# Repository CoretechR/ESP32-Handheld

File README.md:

# ESP32-Handheld

Tested with Arduino for ESP32 Core 1.0.4

The lastes firmware needs the modified Adafruit SharpMem library. This library includes a hugely faster screen clearing function and hardware SPI.

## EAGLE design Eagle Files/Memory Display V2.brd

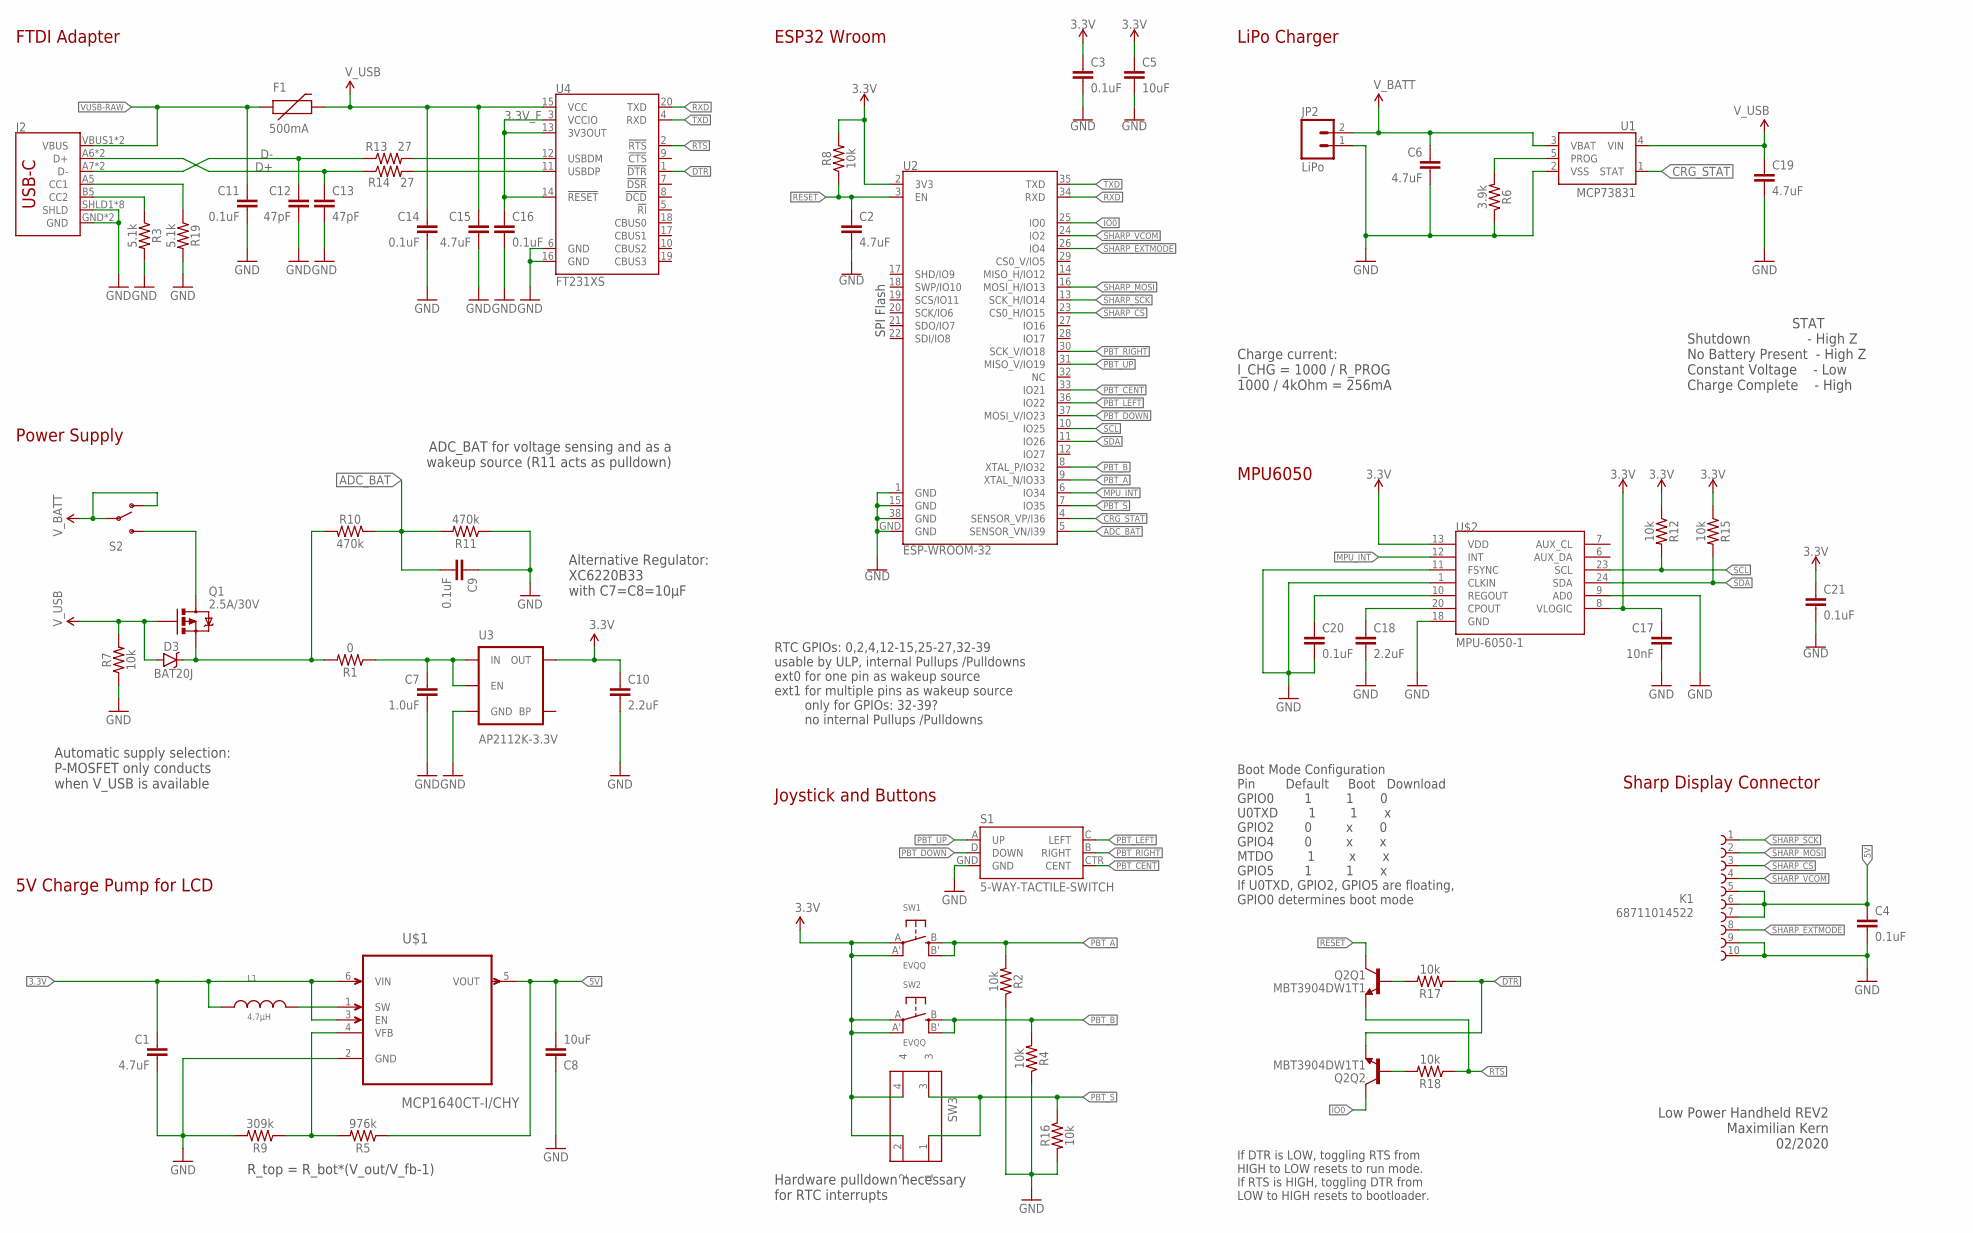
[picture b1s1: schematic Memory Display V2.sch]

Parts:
C1, C2, C6, C19: 4.7uF; 0603
C3, C4, C9, C11, C14, C16, C20, C21: 0.1uF; 0603
C5, C8: 10uF; 0603
C7: 1.0uF; 0805
C10, C18: 2.2uF; 0805
C12, C13: 47pF; 0603
C15: 4.7uF; 0603-CAP
C17: 10nF; 0603
D3: BAT20J; SOD-323
F1: 500mA; PTC-1206
J2: USB_C16PIN; USB-C-16P
JP2: LiPo; JST-2-PTH
K1: 68711014522
L1: 4.7µH; WE-TPC_2811/2813_OLD
Q1: 2.5A/30V; SOT23-3
Q2: MBT3904DW1T1; SC70-6
R1: 0; 0603
R2, R4, R7, R8, R12, R15, R16, R17, R18: 10k; 0603
R3, R19: 5.1k; 0603
R5: 976k; 0603
R6: 3.9k; 0603
R9: 309k; 0603
R10, R11: 470k; 0603
R13, R14: 27; 0603
S1: 5-WAY-TACTILE-SWITCH; JOYSTICK_MINI
S2: SWITCH-SPDT-SMD-A; SWITCH-SPST-SMD-A
SW1, SW2: EVQQ; EVQ-Q2_SMALLER
SW3: 434331045822
U1: MCP73831; SOT23-5
U2: ESP-WROOM-32
U3: AP2112K-3.3V; SOT23-5
U4: FT231XS; SSOP20_L
U$1: MCP1640CT-I/CHY; SOT95P270X145-6N
U$2: MPU-6050-1; QFN-24-4MM2

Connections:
3.3V: C1.1, C3.1, C5.1, C10.1, C17.1, C21.1, L1.1, R8.2, R12.1, R15.1, SW1.A, SW1.A' (P1), SW2.A, SW2.A' (P1), SW3.2, SW3.4, U2.2 (3V3), U3.5 (OUT), U$1.3 (EN), U$1.6 (VIN), U$2.8 (VLOGIC), U$2.13 (VDD)
3.3V_F: C16.1, U4.3 (VCCIO), U4.13 (3V3OUT), U4.14 (!RESET)
5V: C4.1, C8.2, K1.5, K1.6, K1.7, R5.1, U$1.5 (VOUT)
ADC_BAT: C9.2, R10.1, R11.2, U2.5 (SENSOR_VN/I39)
B_VFB: R5.2, R9.1, U$1.4 (VFB)
CRG_STAT: U1.1 (STAT), U2.4 (SENSOR_VP/I36)
D+: C13.1, J2.A6 (D+), J2.B6 (D+), R14.1
D-: C12.1, J2.A7 (D-), J2.B7 (D-), R13.1
DTR: Q2.1 (E), R17.1, U4.1 (!DTR)
GND: C1.2, C2.2, C3.2, C4.2, C5.2, C6.2, C7.2, C8.1, C9.1, C10.2, C11.2, C12.2, C13.2, C14.2, C15.2, C16.2, C17.2, C18.2, C19.2, C20.2, C21.2, J2.GND, J2.GND2 (GND), J2.SHLD1 (SHLD), J2.SHLD2 (SHLD), J2.SHLD3 (SHLD), J2.SHLD4 (SHLD), J2.SHLD5 (SHLD), J2.SHLD6 (SHLD), J2.SHLD7 (SHLD), J2.SHLD8 (SHLD), JP2.1, K1.9, K1.10, R2.1, R3.2, R4.1, R6.1, R7.1, R9.2, R11.1, R16.2, R19.2, S1.GND, U1.2 (VSS), U2.1 (GND), U2.15 (GND), U2.38 (GND), U2.GND, U3.2 (GND), U4.6 (GND), U4.16 (GND), U$1.2 (GND), U$2.1 (CLKIN), U$2.9 (AD0), U$2.11 (FSYNC), U$2.18 (GND)
IO0: Q2.6 (C), U2.25 (IO0)
MPU_INT: U2.6 (IO34), U$2.12 (INT)
unnamed: L1.2, U$1.1 (SW)
unnamed: C7.1, R1.1, U3.1 (IN), U3.3 (EN)
unnamed: Q1.3 (D), S2.3 (S)
unnamed: D3.C, Q1.2 (S), R1.2, R10.2
unnamed: R13.2, U4.12 (USBDM)
unnamed: R14.2, U4.11 (USBDP)
unnamed: J2.A5 (CC1), R19.1
unnamed: Q2.5 (B), R17.2
unnamed: J2.B5 (CC2), R3.1
unnamed: Q2.2 (B), R18.2
unnamed: R6.2, U1.5 (PROG)
unnamed: C18.1, U$2.20 (CPOUT)
unnamed: C20.1, U$2.10 (REGOUT)
PBT_A: R2.2, SW1.B (S), SW1.B' (S1), U2.9 (XTAL_N/IO33)
PBT_B: R4.2, SW2.B (S), SW2.B' (S1), U2.8 (XTAL_P/IO32)
PBT_CENT: S1.CTR (CENT), U2.33 (IO21)
PBT_DOWN: S1.D (DOWN), U2.37 (MOSI_V/IO23)
PBT_LEFT: S1.C (LEFT), U2.36 (IO22)
PBT_RIGHT: S1.B (RIGHT), U2.30 (SCK_V/IO18)
PBT_S: R16.1, SW3.1, SW3.3, U2.7 (IO35)
PBT_UP: S1.A (UP), U2.31 (MISO_V/IO19)
RESET: C2.1, Q2.3 (C), R8.1, U2.3 (EN)
RTS: Q2.4 (E), R18.1, U4.2 (!RTS)
RXD: U2.34 (RXD), U4.20 (TXD)
SCL: R12.2, U2.10 (IO25), U$2.23 (SCL)
SDA: R15.2, U2.11 (IO26), U$2.24 (SDA)
SHARP_CS: K1.3, U2.23 (CS0_H/IO15)
SHARP_EXTMODE: K1.8, U2.26 (IO4)
SHARP_MOSI: K1.2, U2.16 (MOSI_H/IO13)
SHARP_SCK: K1.1, U2.13 (SCK_H/IO14)
SHARP_VCOM: K1.4, U2.24 (IO2)
TXD: U2.35 (TXD), U4.4 (RXD)
VUSB-RAW: C11.1, F1.1, J2.VBUS1 (VBUS), J2.VBUS2 (VBUS)
V_BATT: C6.1, JP2.2, S2.1 (O), S2.2, U1.3 (VBAT)
V_USB: C14.1, C15.1, C19.1, D3.A, F1.2, Q1.1 (G), R7.2, U1.4 (VIN), U4.15 (VCC)

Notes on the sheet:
ESP32 Wroom
Boot Mode Configuration Pin Default Boot Download GPIO0 1 1 0 U0TXD 1 1 x GPIO2 0 x 0 GPIO4 0 x x MTDO 1 x x GPIO5 1 1 x If U0TXD, GPIO2, GPIO5 are floating, GPIO0 determines boot mode
If DTR is LOW, toggling RTS from HIGH to LOW resets to run mode. If RTS is HIGH, toggling DTR from LOW to HIGH resets to bootloader.
Charge current: I_CHG = 1000 / R_PROG 1000 / 4kOhm = 256mA
Power Supply
FTDI Adapter
LiPo Charger
Joystick and Buttons
5V Charge Pump for LCD
RTC GPIOs: 0,2,4,12-15,25-27,32-39 usable by ULP, internal Pullups /Pulldowns ext0 for one pin as wakeup source ext1 for multiple pins as wakeup source only for GPIOs: 32-39? no internal Pullups /Pulldowns
SPI Flash
Low Power Handheld REV2 Maximilian Kern 02/2020
STAT Shutdown - High Z No Battery Present - High Z Constant Voltage - Low Charge Complete - High
ADC_BAT for voltage sensing and as a wakeup source (R11 acts as pulldown)
R_top = R_bot*(V_out/V_fb-1)
Sharp Display Connector
MPU6050
Alternative Regulator: XC6220B33 with C7=C8=10µF
Automatic supply selection: P-MOSFET only conducts when V_USB is available
Hardware pulldown necessary for RTC interrupts

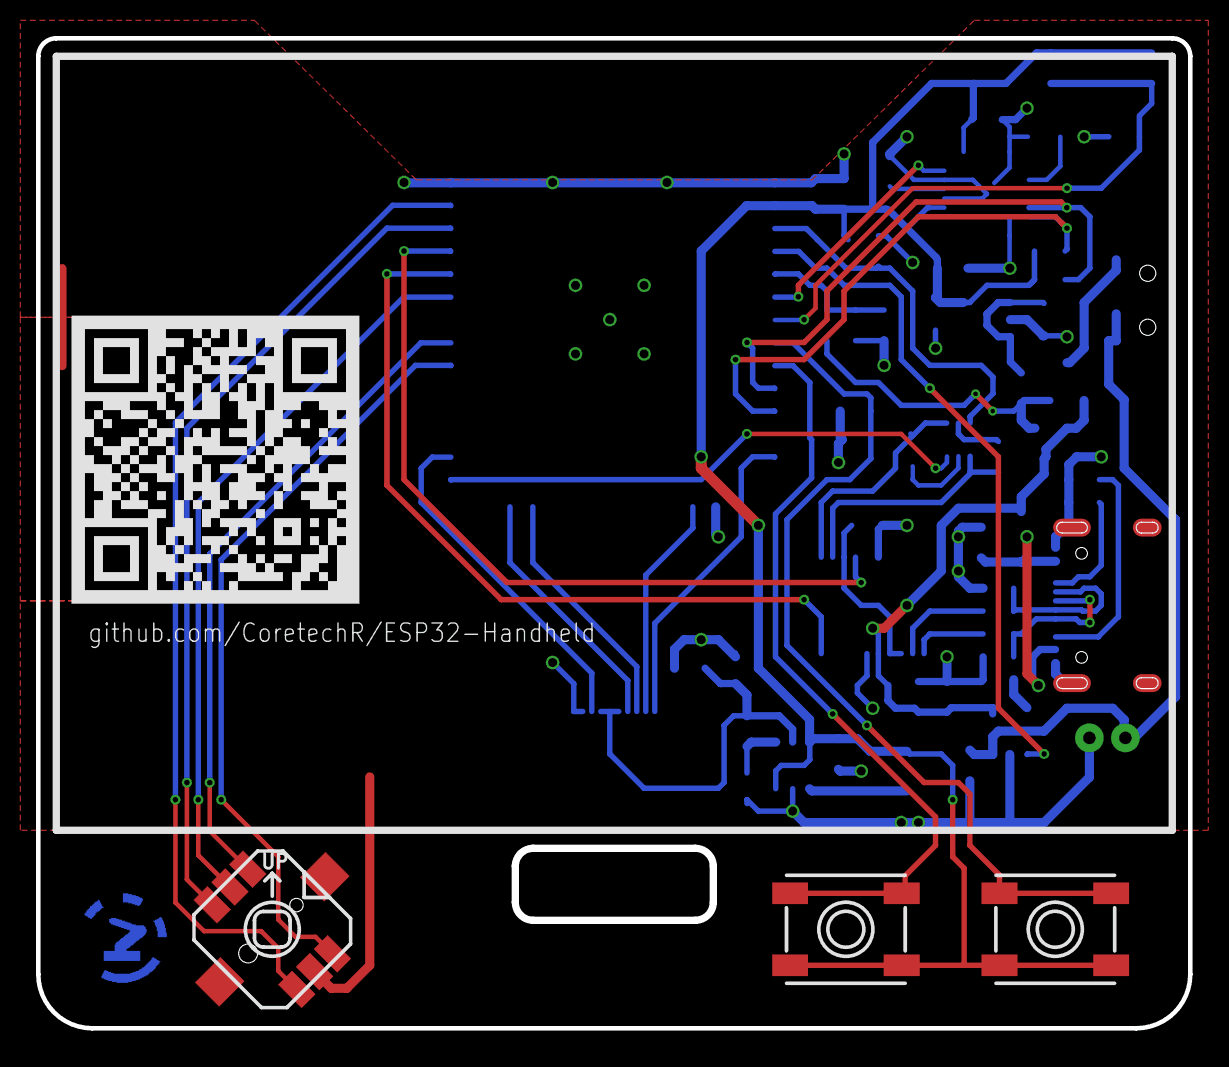
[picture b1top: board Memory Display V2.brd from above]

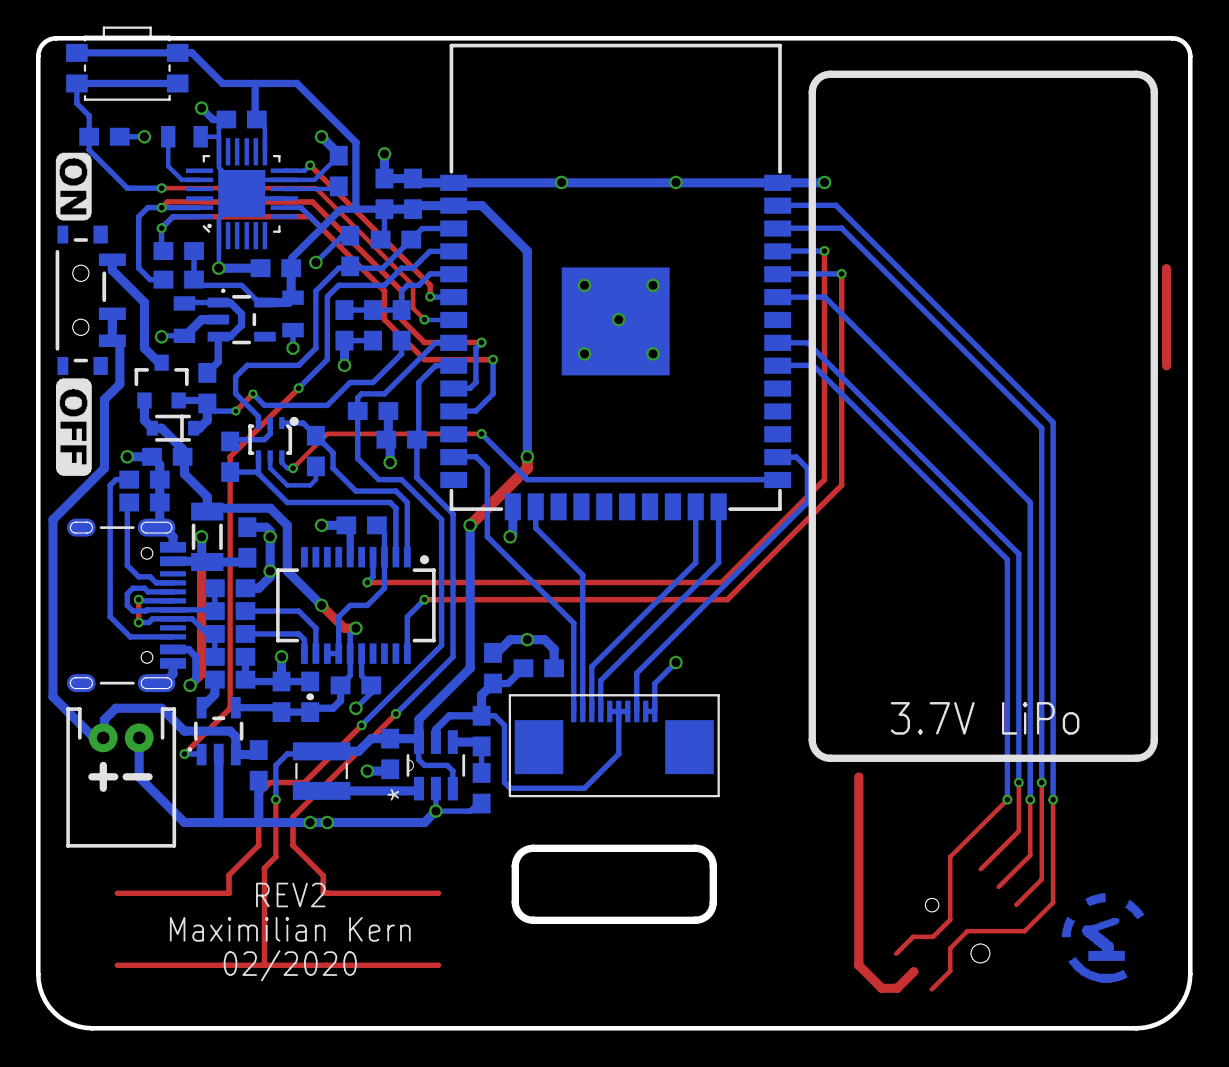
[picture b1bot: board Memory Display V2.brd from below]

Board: 2 copper layers, 63.8 x 54.8 mm, 59 parts (56 on the bottom side), 47 nets.

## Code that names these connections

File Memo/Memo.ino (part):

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#define WIDTH 400
#define HEIGHT 240

#define SHARP_SCK  14
#define SHARP_MOSI 13
#define SHARP_SS   15

#define I2C_SDA 26
#define I2C_SCL 25
#define INTP 34

#define ADC_BAT 39
#define CRG_STAT 36

#define ABUT 33
#define BBUT 32
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  pinMode(CBUT, INPUT_PULLUP);
  pinMode(SBUT, INPUT_PULLUP);

  pinMode(CRG_STAT, INPUT);
  pinMode(ADC_BAT, INPUT);
  pinMode(INTP, INPUT_PULLUP);
  adcAttachPin(CRG_STAT);
  adcAttachPin(ADC_BAT);
  analogReadResolution(12);
  analogSetWidth(12);
  analogSetAttenuation(ADC_11db);
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
void Task1code( void * pvParameters ){
  for(;;){
    adcAttachPin(CRG_STAT);
    adcAttachPin(ADC_BAT);
    analogReadResolution(12);
    analogSetWidth(12);
    analogSetAttenuation(ADC_11db);
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
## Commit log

2019-12-15 Create Eagle Files
2019-12-15 Create Test
2019-12-17 Create LICENSE
2020-03-19 firmware for REV2 released
    Better performance (modified adafruit sharpmem library needed)
    Gyro Support and more "tech demo" apps
2020-03-19 REV2 release
    Added the MPU6050 and a shoulder button
    Battery cable connector moved to bottom
2020-03-19 Added gifs of how the gyro can be utilized
2020-03-20 Added modified Adafruit SharpMem
    This library contains an improved function to fill the screen by writing to the display buffer directly.
    Also uses Hardware SPI (no major improvement over software sadly)
2020-07-12 V7 - BLE ANCS Notifications added

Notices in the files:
parts and their libraries:
SparkFun-Electromechanical: Licensing: CC v3.0 Share-Alike You are welcome to use this library for commercial purposes.
SparkFun-RF: Licensing: Creative Commons ShareAlike 4.0 International - https://creativecommons.org/licenses/by-sa/4.0
EMCComponents: Copyright: Würth Elektronik
